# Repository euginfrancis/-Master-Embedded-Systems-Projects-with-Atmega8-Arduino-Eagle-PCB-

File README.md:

# Master Embedded Systems: Projects with Atmega328, Arduino, and Eagle-PCB

Welcome to the **Embedded Systems Projects** repository! This repository contains a collection of projects using the **Atmega328** microcontroller, **Arduino**, and **Eagle PCB design**. These projects are designed for beginners who want to learn embedded systems concepts, build real-world applications, and fabricate their own PCBs.

## Table of Contents

- [Overview](#overview)
- [Understanding Microcontrollers: Atmega328 Basics](#understanding-microcontrollers-atmega8-basics)
- [Compile a C file using WinAVR](#compile-a-c-file-using-winavr)
- [Programming with Arduino IDE](#programming-with-arduino-ide)
- [Installing Arduino IDE and Setting Up ATmega328/UNO Board](#installing-arduino-ide-and-setting-up-atmega328uno-board)
- [Setting Up USBASP Programmer and USB-to-Serial Converter](#setting-up-usbasp-programmer-and-usb-to-serial-converter)
- [Eagle PCB Design: From Schematic to Fabrication](#eagle-pcb-design-from-schematic-to-fabrication)
- [DIY PCB Fabrication Process](#diy-pcb-fabrication-process)
- [HD44780 LCD Communication Protocol](#hd44780-lcd-communication-protocol)

## Overview

This repository provides practical examples of embedded systems projects using the **Atmega328** microcontroller and **Arduino** platform. You will also explore **Eagle PCB design** for creating custom PCBs. The goal is to build a solid foundation for working with embedded systems and PCB fabrication.

## Understanding Microcontrollers: Atmega8 Basics

A **microcontroller** is a compact integrated circuit that acts as the brain of an embedded system. It combines a processor (for executing instructions), memory (for storing programs and temporary data), and input/output pins (for connecting to external devices) all in one chip. Unlike general-purpose computers, microcontrollers are designed to perform specific tasks, such as controlling an appliance, blinking an LED, or reading data from a sensor. Their versatility and low cost make them a cornerstone of modern electronics, found in everything from toys to industrial machinery.

The **Atmega328**, part of the AVR family, is a popular 8-bit microcontroller for beginners. Built on the efficient AVR architecture, it uses a Reduced Instruction Set Computer (RISC) design for faster performance. It features 32 KB of Flash memory for program storage, 1 KB of SRAM for temporary data, and 512 bytes of EEPROM for saving data even when power is off. With 23 input/output pins, built-in timers, a 10-bit Analog-to-Digital Converter (ADC), and communication protocols like UART, SPI, and I2C, the Atmega328 is ideal for learning how microcontrollers work. Its simplicity, combined with powerful features, makes it a go-to choice for building practical projects like motor control, sensor interfacing, and custom PCB designs.

## Compile a C file using WinAVR

To compile a C file using **WinAVR**, follow these steps:

### Step 1: Install WinAVR

Download and install **WinAVR** from its [official site](http://winavr.sourceforge.net/) or a trusted source.  
This package includes:
- **avr-gcc compiler**
- **avrdude**
- Supporting tools

### Step 2: Write the C Program

Create your C program and save it with a `.c` extension. For example, `main.c`.

### Step 3: Create a Makefile

Create a file named `Makefile` in the same directory as your C program.

Here is a simple example of a Makefile:

```makefile
MCU = atmega8       # Target microcontroller (change as needed)
F_CPU = 16000000UL  # Clock frequency
CC = avr-gcc
CFLAGS = -mmcu=$(MCU) -DF_CPU=$(F_CPU) -Wall -Os
TARGET = main

all: $(TARGET).hex

$(TARGET).hex: $(TARGET).elf
	avr-objcopy -O ihex -R .eeprom $(TARGET).elf $(TARGET).hex

$(TARGET).elf: $(TARGET).c
	$(CC) $(CFLAGS) -o $(TARGET).elf $(TARGET).c

clean:
	rm -f *.elf *.hex
```
### Makefile Explanation:

- `MCU`: Specify your microcontroller model (e.g., atmega8, atmega328p).
- `F_CPU`: Specify the frequency of your microcontroller in Hz.
- Replace `main.c` with the name of your C file if different.

### Step 4: Compile the Program

1. Open a command prompt.
2. Navigate to the folder containing your `main.c` and `Makefile`.
3. Run the `make` command:

```bash
make
```
This will compile your code and generate a .hex file ready for uploading to the microcontroller.

### Step 5: Upload to the Microcontroller

Use avrdude to upload the .hex file to your microcontroller. For example:

```bash
avrdude -c usbasp -p atmega8 -U flash:w:main.hex
```
Replace usbasp with your programmer.
Replace atmega8 with your microcontroller model.

### Step 6: Verify the Program

Ensure your microcontroller runs the compiled program as expected.

### Troubleshooting

If you encounter issues:

    Verify the MCU and F_CPU values match your microcontroller.
    Ensure all paths are set correctly in the environment variables if make or avr-gcc is not recognized.

## Programming with Arduino IDE

Arduino provides several built-in functions to interact with hardware components like LEDs, sensors, and motors. Here’s an overview of the most commonly used functions, explained in a simple way.

### `pinMode()`
Configures a GPIO pin as an **input** or **output**.  
- **pin**: The pin number you want to set (e.g., 2, 13).  
- **mode**: Use `INPUT`, `OUTPUT`, or `INPUT_PULLUP`.  

**Example**:  
```cpp
pinMode(13, OUTPUT); // Set pin 13 as output
pinMode(2, INPUT);   // Set pin 2 as input
```
### `digitalWrite()`
Sets a pin to either HIGH (on) or LOW (off).

**Example**:  
```cpp
digitalWrite(13, HIGH); // Turn on LED connected to pin 13
digitalWrite(13, LOW);  // Turn it off
```
### `digitalRead()`
Reads the state of a digital input pin (HIGH or LOW).

**Example**:  
```cpp
int buttonState = digitalRead(2); // Read the state of the button on pin 2
```
### `analogWrite()`
Generates a PWM signal to control the brightness of LEDs or the speed of motors.

value: Ranges from 0 (off) to 255 (full brightness or speed).

**Syntax**:
```cpp
analogWrite(pin, value);
```

**Example**:
```cpp
analogWrite(9, 128); // Set 50% brightness on pin 9
```
### `delay()`
Pauses the program for a specified time in milliseconds.

**Syntax**:
```cpp
delay(milliseconds);
```

**Example**:
```cpp
delay(1000); // Wait for 1 second
```
### `Serial.begin`()
Initializes communication between the Arduino and a computer. The baud rate determines the speed of communication (e.g., 9600 bits per second).

**Syntax**:
```cpp
Serial.begin(baudRate);
```

**Example**:
```cpp
Serial.begin(9600); // Start communication at 9600 bps
```
### `Serial.print() and Serial.println()`
Send data or messages to the computer via the Serial Monitor.
Serial.print(): Prints data on the same line.
Serial.println(): Prints data and moves to the next line.

**Example**:
```cpp
Serial.print("Temperature: ");
Serial.println(25);
```
### `Serial.read()`
Reads incoming data from the serial buffer (one byte at a time).

**Syntax**:
```cpp
char data = Serial.read();
```
**Example**:
```cpp
if (Serial.available() > 0) {
    char receivedData = Serial.read(); // Read the first available byte
}
```

## Installing Arduino IDE and Setting Up ATmega328/UNO Board

This guide provides a brief explanation on how to install the Arduino IDE and set up the **ATmega328** or **Arduino Uno** board.

### 1. Install the Arduino IDE

#### a. Download and Install
1. Visit the official [Arduino website](https://www.arduino.cc/en/software).
2. Download the appropriate version for your operating system (Windows, macOS, Linux).
3. Follow the installation instructions:
   - For Windows: Run the installer `.exe` file and follow the prompts.
   - For macOS: Open the `.dmg` file and drag the Arduino IDE to the Applications folder.
   - For Linux: Use the package manager or install from the tarball.

#### b. Launch the IDE
After installation, launch the **Arduino IDE**. You should see the Arduino IDE window ready for use.

### 2. Set Up the ATmega328/UNO Board in Arduino IDE

#### a. Open the Arduino IDE
1. Open the **Arduino IDE** after installation.

#### b. Select the Board (ATmega328/UNO)
1. Go to **Tools** → **Board** → **Arduino Uno** (which uses the ATmega328P microcontroller).
2. Select **Arduino Uno** from the list of available boards.

#### c. Select the Port
1. Connect your **Arduino Uno** to your computer using a USB cable.
2. Go to **Tools** → **Port** and select the correct port where your Arduino Uno is connected. On Windows, this is usually something like `COM3` or `COM4`. On macOS/Linux, it will show up as `/dev/cu.usbmodemXXXX`.

### 3. Install the ATmega328 Drivers (if needed)

If your Arduino Uno is not recognized or you're using a clone board, you may need to install drivers.

- **For Windows**: The drivers are automatically installed when you install the Arduino IDE. However, for clone boards, you may need to manually install the **CH340/CH341** driver from the manufacturer's website.
- **For macOS/Linux**: These platforms usually don’t require additional drivers. If needed, you can find open-source drivers or use tools like **brew** on macOS.

### 4. Test the Setup

To confirm everything is set up correctly:

1. Open the **Arduino IDE**.
2. Go to **File** → **Examples** → **01.Basics** → **Blink**.
3. Click the **Upload** button (right arrow icon).
4. The LED on pin 13 of the Arduino Uno should start blinking if everything is configured properly.

You have now successfully set up the Arduino IDE for programming the **ATmega328/Uno** board.

## Setting Up USBASP Programmer and USB-to-Serial Converter

This guide explains how to set up the **USBASP programmer** for programming an ATmega328 on a custom PCB and the **USB-to-serial converter** to read data from the board using the **Arduino IDE**.

### 1. Setting Up USBASP Programmer

#### a. Connect the USBASP Programmer to the ATmega328
1. **USBASP Pin Connections**:
   - **MISO** (Master In Slave Out) → **MISO** pin of ATmega328
   - **MOSI** (Master Out Slave In) → **MOSI** pin of ATmega328
   - **SCK** (Serial Clock) → **SCK** pin of ATmega328
   - **RESET** → **RESET** pin of ATmega328
   - **VCC** → **VCC** pin of ATmega328 (5V)
   - **GND** → **GND** pin of ATmega328

2. Ensure that the **USBASP** programmer is securely connected to the **ISP header** (In-System Programming) of your custom PCB.

#### b. Install USBASP Drivers
If your computer does not automatically recognize the **USBASP programmer**, you may need to install drivers:

- **For Windows**: Download and install the **USBASP drivers** from [fischl.de](http://www.fischl.de/usbasp/).
- **For macOS/Linux**: These platforms typically don't require drivers. If needed, you can install **libusb** or use open-source drivers.

#### c. Select USBASP Programmer in Arduino IDE
1. Open **Arduino IDE**.
2. Go to **Tools** → **Programmer** → Select **USBasp**.

### 2. Setting Up USB-to-Serial Converter

#### a. Connect the USB-to-Serial Converter to the ATmega328
To read data from the ATmega328 on your custom PCB, you can use a **USB-to-Serial converter** (e.g., FTDI or CP2102). Here’s how to connect the pins:

1. **USB-to-Serial Pin Connections**:
   - **TX (Transmit)** → **RX** pin of ATmega328
   - **RX (Receive)** → **TX** pin of ATmega328
   - **VCC** → **VCC** pin of ATmega328 (5V)
   - **GND** → **GND** pin of ATmega328
   
2. Make sure the **USB-to-Serial converter** is connected to your PC via USB, and the other side is connected to the ATmega328.

#### b. Select the Serial Port in Arduino IDE
1. Go to **Tools** → **Port** and select the correct COM port for your USB-to-Serial device.
   - On Windows, this could be something like `COM3` or `COM4`.
   - On macOS/Linux, it will be `/dev/cu.usbserial-xxxx`.

#### c. Upload Code and Read Data via Serial Monitor
1. Write your program in **Arduino IDE** and upload it to the ATmega328.
2. Open **Tools** → **Serial Monitor** in Arduino IDE to view data transmitted via **Serial Communication**.
3. Use `Serial.print()` or `Serial.println()` in your program to send data to the **Serial Monitor**.

### 3. Uploading the Program to the ATmega328

### a. Using USBASP Programmer
1. Connect the **USBASP** programmer to your custom PCB.
2. Select **Tools** → **Board** → **Arduino Uno** (for ATmega328).
3. Select **Tools** → **Programmer** → **USBasp**.
4. Click the **Upload Using Programmer** button (Shift + Upload button) to upload the code to the ATmega328.

#### b. Reading Data via Serial Monitor
1. Once the code is uploaded, you can monitor the output of your ATmega328 using **Serial Monitor** (set baud rate as per your code, e.g., 9600).
2. Use `Serial.print()` in your program to send real-time data to the Serial Monitor for debugging or display purposes.

### 4. Troubleshooting

- **USBASP Not Recognized**: If your **USBASP** is not recognized, ensure the drivers are properly installed. On Windows, check for any driver conflicts in the **Device Manager**.
- **No Output on Serial Monitor**: If you're not seeing data in the **Serial Monitor**, check the **TX/RX** connections between the **USB-to-Serial converter** and the **ATmega328**. Also, ensure the baud rate in the `Serial.begin()` matches the baud rate set in the **Serial Monitor**.

## Eagle PCB Design: From Schematic to Fabrication

This guide explains how to use **Eagle PCB Design Software** to create a schematic, design a PCB, and prepare it for fabrication.

### 1. Creating the Schematic in Eagle

1. **Open Eagle Software** and create a new project.
2. In the **Control Panel**, right-click on the project folder and select **New** → **Schematic**.
3. Add components by clicking on the **Add Part** tool, search for components (e.g., resistors, capacitors, ICs) from the libraries.
4. Use the **Wire** tool to connect the components as per your circuit design.
5. Label your nets using the **Label** tool to make the connections clear.
6. Once the schematic is complete, run the **ERC (Electrical Rule Check)** to ensure there are no errors in the design.

### 2. Designing the PCB Layout

1. After completing the schematic, switch to the **PCB Layout** by clicking on the **Switch to Board** button.
2. Eagle will automatically create a board outline, but you can customize it according to your needs.
3. Arrange the components on the board, making sure to keep routing clean and components placed logically.
4. Use the **Route** tool to draw the PCB traces, connecting the components' pins.
5. Add a **Ground Plane** using the **Polygon** tool to reduce noise and improve stability.

### 3. Checking and Finalizing the Design

1. Run the **DRC (Design Rule Check)** to verify that the traces and components meet the fabrication requirements (e.g., trace width, spacing).
2. Use the **Electrical Rule Check (ERC)** to ensure there are no electrical issues.
3. Once everything looks good, generate the **Gerber Files** required for PCB fabrication.

### 4. Fabricating the PCB

1. Export the Gerber files by going to **File** → **CAM Processor**, then selecting the required file outputs (e.g., **Top Layer**, **Bottom Layer**, **Solder Mask**, **Drill Files**).
2. Send the Gerber files to a PCB fabrication service. There are several online services available for custom PCB manufacturing.
3. After the PCB is fabricated, you can solder the components and test the board for functionality.

## DIY PCB Fabrication Process

This guide will walk you through the steps for fabricating a **Printed Circuit Board (PCB)** at home using a **laser printer**, **iron box (clothes iron)**, **ferric chloride (etchant)**, and manual drilling for holes.

### Materials Needed:
- **Laser Printer** (for printing your PCB design)
- **Parchment Paper** (or glossy photo paper)
- **Iron Box** (for transferring toner to the PCB)
- **Ferric Chloride Solution** (for etching the PCB)
- **Copper-Clad PCB Board** (for the base material)
- **Fine Sandpaper** (to clean the PCB)
- **Drill** (for manually drilling holes)
- **Acetone** (for cleaning the PCB)
- **Masking Tape** (optional, to hold the paper in place)

### Step 1: Design the PCB

1. **Create the PCB Design**: Use PCB design software like **Eagle**, **KiCad**, or **EasyEDA** to design your circuit schematic and PCB layout.
2. **Export the Design**: Once your design is ready, export it as a **mirror image** (in Gerber or PDF format) to ensure proper alignment during the transfer.

### Step 2: Print the PCB Design

1. **Print the Design**: Print your mirrored PCB design onto **glossy photo paper** or **parchment paper** using a **laser printer**. Inkjet printers won't work for this method because toner is required to transfer to the PCB.
2. **Print at High Quality**: Ensure you select the highest print quality and set the paper to **no scaling** to preserve the exact size of your design.

### Step 3: Prepare the Copper-Clad PCB

1. **Clean the PCB**: Use **fine sandpaper** to gently sand the surface of the **copper-clad PCB**. This helps the toner adhere better.
2. **Clean the Board**: After sanding, clean the board with **acetone** or rubbing alcohol to remove any grease, dust, or debris.

### Step 4: Transfer the Toner

1. **Position the Printed Design**: Place the printed design (toner side down) onto the copper surface of the PCB. Ensure it aligns correctly.
2. **Secure the Paper**: Use **masking tape** to hold the paper in place if necessary.
3. **Iron the Paper onto the PCB**:
   - Preheat the **iron box** to a medium-high heat setting (no steam).
   - Press the iron firmly onto the paper for about **3-5 minutes**, ensuring that the heat is evenly distributed over the entire design.
   - Apply even pressure and make small circular movements to ensure good contact.
4. **Check the Transfer**: After a few minutes, peel off the paper. The toner should have transferred to the PCB, leaving the copper areas exposed for etching.

### Step 5: Etch the PCB

1. **Prepare Ferric Chloride Solution**: Mix **ferric chloride** with water (usually 1 part ferric chloride to 3 parts water). You can use a plastic or glass container to hold the solution.
2. **Submerge the PCB**: Place the PCB in the **ferric chloride solution**. Gently agitate the container to help the etching process.
3. **Wait for the Etching Process**: The ferric chloride will dissolve the exposed copper, leaving the toner-protected copper traces intact. This usually takes about **30 minutes to 1 hour**.
4. **Check Progress**: Periodically check the progress. Once all the exposed copper is etched away and only the toner traces remain, remove the PCB from the solution.

### Step 6: Clean and Finalize the PCB

1. **Remove the Toner**: After etching, the PCB will be covered in toner. Use **acetone** to remove the toner and reveal the copper traces.
2. **Drill Holes**: For components that require through-hole connections, carefully drill the holes using a small **drill bit**. You can use a handheld drill or a Dremel tool.
   - Make sure to use the correct bit size for the components' lead diameter.
   - Keep the PCB steady and drill at a slow speed to avoid damaging the traces.

### Step 7: Inspect the PCB

1. **Inspect for Errors**: Carefully inspect the PCB for any missed connections, broken traces, or incomplete etching. You can fix minor issues with **conductive ink** or **wire bridges**.
2. **Test the PCB**: Before soldering components, it's a good idea to test the board with a multimeter to ensure the traces and connections are correct.

### Conclusion

Congratulations! You've just fabricated your own **PCB** at home. Now, you can proceed with **soldering the components** onto the PCB, and your custom circuit is ready to be used. While this process can take some time, it's a great and cost-effective way to create your own PCBs without needing a professional service.

## HD44780 LCD Communication Protocol

### Initialization Sequence (Setting up the LCD)

```mermaid
sequenceDiagram
    participant MCU
    participant LCD

    MCU->>LCD: Send Function Set (e.g., 0x38)
    LCD->>MCU: Acknowledge

    MCU->>LCD: Send Display ON/OFF (e.g., 0x0C)
    LCD->>MCU: Acknowledge

    MCU->>LCD: Send Clear Display Command (e.g., 0x01)
    LCD->>MCU: Acknowledge

    MCU->>LCD: Send Entry Mode Set (e.g., 0x06)
    LCD->>MCU: Acknowledge

    MCU->>LCD: Send Cursor Home Command (e.g., 0x02)
    LCD->>MCU: Acknowledge

    MCU->>MCU: LCD Initialized

```
### Write Command Sequence (Sending Command to LCD)

```mermaid
sequenceDiagram
    participant MCU
    participant LCD

    MCU->>LCD: Send Command (e.g., 0x80 for setting cursor)
    LCD->>MCU: Acknowledge
    MCU->>LCD: Send Command Data (e.g., character or special instruction)
    LCD->>MCU: Acknowledge
    MCU->>MCU: Command Executed (cursor moved or action performed)
```

### Read Command Sequence (Reading Status or Data from LCD)

```mermaid
sequenceDiagram
    participant MCU
    participant LCD

    MCU->>LCD: Send Read Command (e.g., 0x80 for status)
    LCD->>MCU: Provide Busy Flag (if LCD is busy)
    
    MCU->>LCD: Send Data Read Command (e.g., 0x00 for data register)
    LCD->>MCU: Return Data (e.g., character from display)
    MCU->>MCU: Read Data Successfully
```

### Write Data String Sequence (Sending a Data String to LCD for Display)

```mermaid
sequenceDiagram
    participant MCU
    participant LCD

    MCU->>LCD: Send Data (e.g., First Character)
    LCD->>MCU: Acknowledge
    MCU->>LCD: Send Next Data Character
    LCD->>MCU: Acknowledge
    loop Write Entire String
        MCU->>LCD: Send Character
        LCD->>MCU: Acknowledge
    end
    MCU->>MCU: Data String Displayed on LCD
```

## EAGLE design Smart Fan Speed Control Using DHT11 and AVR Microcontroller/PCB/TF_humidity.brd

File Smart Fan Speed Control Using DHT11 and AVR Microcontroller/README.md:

# Smart Fan Speed Control Using DHT11 and AVR Microcontroller

This project demonstrates how to control the speed of a fan based on room temperature readings from a **DHT11 sensor**. The speed of the fan is controlled using **Pulse Width Modulation (PWM)** through an **AVR microcontroller**. This guide explains how to set up the hardware and software for this project, along with the necessary flashing and PCB creation steps.

## Components Used
- **AVR Microcontroller** (e.g., ATmega328P)
- **DHT11 Temperature and Humidity Sensor**
- **PWM-Controlled Fan**
- **NPN Transistor (e.g., 2N2222) or MOSFET** (for controlling the fan)
- **Resistors, Capacitors, and other Passive Components**

## DHT11 Sensor Details

The **DHT11** sensor is a basic, low-cost digital sensor used for measuring temperature and humidity. It communicates with a microcontroller using a **single-wire digital interface**, sending data as a **serial stream** of 40 bits.

### Key Features of DHT11:
- **Temperature Range**: 0°C to 50°C (accuracy: ±2°C)
- **Humidity Range**: 20% to 90% RH (accuracy: ±5% RH)
- **Output**: Digital (serial)
- **Operating Voltage**: 3.5V to 5.5V

### DHT11 Communication Protocol
The DHT11 sensor uses a **single-wire communication protocol** to transmit data. The sensor sends data in **40 bits**:
1. **Humidity (16 bits)**: The first 16 bits represent humidity data.
2. **Temperature (16 bits)**: The next 16 bits represent temperature data.
3. **Checksum (8 bits)**: The last 8 bits are a checksum to verify the accuracy of the data.

To communicate with the DHT11 sensor, the microcontroller sends a **start signal** to the sensor, which responds with the requested data.

### DHT11 Communication Sequence Diagram

```mermaid
%% Example of a timing diagram for a start signal
sequenceDiagram
    participant MCU
    participant Sensor
    
    MCU->>Sensor: Send Start Signal (18ms Low)
    Sensor->>MCU: Respond (80µs Low, 80µs High)
    MCU->>Sensor: Wait for Data
    Sensor->>MCU: Send Data (40 bits)
    MCU->>MCU: Validate Data Integrity
    MCU->>Sensor: Return Success/Failure

```

## Project Overview

This project reads the room temperature from the DHT11 sensor, then adjusts the fan speed accordingly using **PWM**. The fan speed increases with higher temperatures, providing an effective and efficient cooling system. The control is implemented using an **AVR microcontroller** (e.g., ATmega328P) which reads the DHT11 sensor and adjusts the PWM signal for fan control.

## Flashing the Code
To flash the code to your AVR microcontroller, you can follow the instructions below:

Install WinAVR:

WinAVR includes the avr-gcc compiler and other tools required to program your AVR microcontroller. Follow the installation guide in the main repository README.

## Program the Microcontroller:

For Arduino: You can use the Arduino IDE to upload the code to your AVR microcontroller. Select the correct board and port in the Tools menu, then click Upload.

For WinAVR: Open a command prompt and use avr-gcc and avrdude to compile and upload the code. Example:

```bash
avr-gcc -mmcu=atmega328p -o program.elf program.c
avr-objcopy -O ihex program.elf program.hex
avrdude -c usbasp -p m328p -U flash:w:program.hex
```
## Flashing Details and Custom PCB Creation

For detailed flashing instructions, please refer to the main repository README.

## Custom PCB Creation: 

If you wish to create a custom PCB for this project, you can follow the steps provided in the main repository. The PCB design can be created using Eagle PCB as outlined in the repository.

## Troubleshooting
If the fan does not adjust speed:

Verify that the PWM pin is properly connected.
Ensure that the DHT11 sensor is connected correctly to the microcontroller.
Check if the microcontroller is properly powered.
If the DHT11 sensor gives inaccurate readings:

Ensure that the DHT11 sensor is connected properly.
Confirm that the sensor's data line is connected to the correct digital pin.

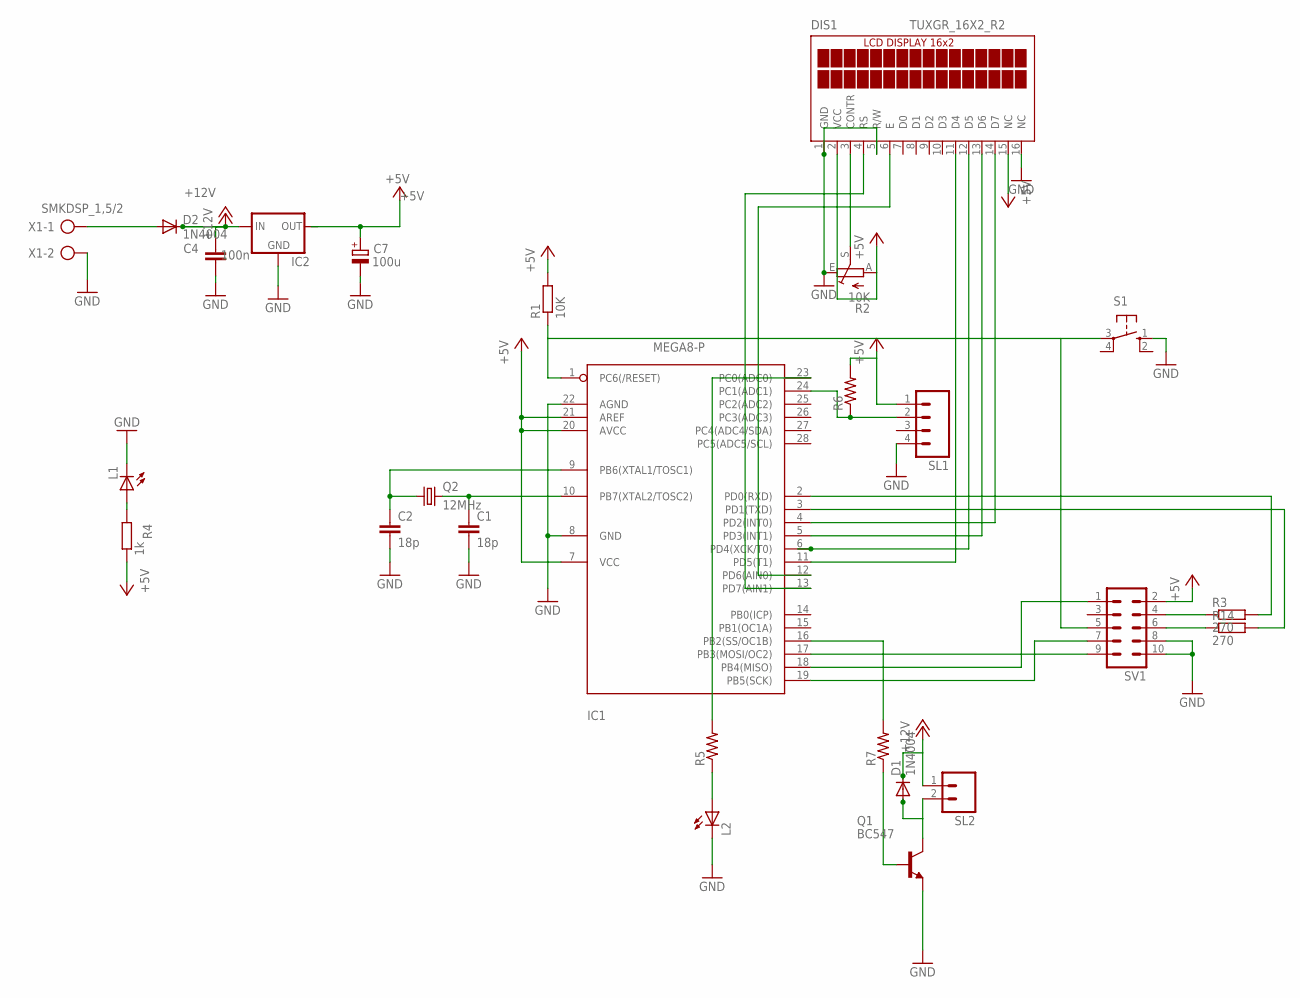
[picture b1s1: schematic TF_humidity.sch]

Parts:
C1, C2: 18p; C025-024X044
C4: 100n; C025-030X050
C7: 100u; E3,5-8
D1, D2: 1N4004; DO41-10
DIS1: TUXGR_16X2_R2
IC1: MEGA8-P; DIL28-3
IC2: 78XXS
L1, L2: LED5MM
Q1: BC547; TO92
Q2: 12MHz; HC49/S
R1: 10K; 0207/10
R2: 10K; CA6V
R3, R14: 270; 0207/10
R4: 1k; 0207/10
R5, R6, R7: R-US_0207/10; 0207/10
S1: 10-XX; B3F-10XX
SL1: M04; 04P
SL2: M02; 02P
SV1: ML10
X1: SMKDSP_1,5/2

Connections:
+5V: C7.+, DIS1.2 (VCC), DIS1.15 (NC), IC1.7 (VCC), IC1.20 (AVCC), IC1.21 (AREF), IC2.OUT, R1.2, R2.A, R4.2, R6.2, SL1.1, SV1.2
+12V: C4.2, D1.C, D2.C, IC2.IN, SL2.1
GND: C1.2, C2.2, C4.1, C7.-, DIS1.1 (GND), DIS1.5 (R/W), DIS1.16 (NC), IC1.8 (GND), IC1.22 (AGND), IC2.GND, L1.K (C), L2.K (C), Q1.1 (E), R2.E, S1.1 (S), SL1.4, SV1.8, SV1.10, X1.2
unnamed: L1.A, R4.1
unnamed: DIS1.6 (E), IC1.12 (PD6(AIN0))
unnamed: C1.1, IC1.10 (PB7(XTAL2/TOSC2)), Q2.2
unnamed: C2.1, IC1.9 (PB6(XTAL1/TOSC1)), Q2.1
unnamed: DIS1.3 (CONTR), R2.S
unnamed: R3.1, SV1.4
unnamed: IC1.2 (PD0(RXD)), R3.2
unnamed: D1.A, Q1.3 (C), SL2.2
unnamed: DIS1.13 (D6), IC1.5 (PD3(INT1))
unnamed: DIS1.14 (D7), IC1.4 (PD2(INT0))
unnamed: IC1.18 (PB4(MISO)), SV1.1
unnamed: DIS1.12 (D5), IC1.6 (PD4(XCK/T0))
unnamed: IC1.1 (PC6(/RESET)), R1.1, S1.3, SV1.5
unnamed: DIS1.11 (D4), IC1.11 (PD5(T1))
unnamed: IC1.17 (PB3(MOSI/OC2)), SV1.9
unnamed: L2.A, R5.1
unnamed: IC1.16 (PB2(SS/OC1B)), R7.2
unnamed: IC1.23 (PC0(ADC0)), R5.2
unnamed: IC1.24 (PC1(ADC1)), R6.1, SL1.2
unnamed: D2.A, X1.1
unnamed: IC1.3 (PD1(TXD)), R14.2
unnamed: R14.1, SV1.6
unnamed: DIS1.4 (RS), IC1.13 (PD7(AIN1))
unnamed: Q1.2 (B), R7.1
unnamed: IC1.19 (PB5(SCK)), SV1.7

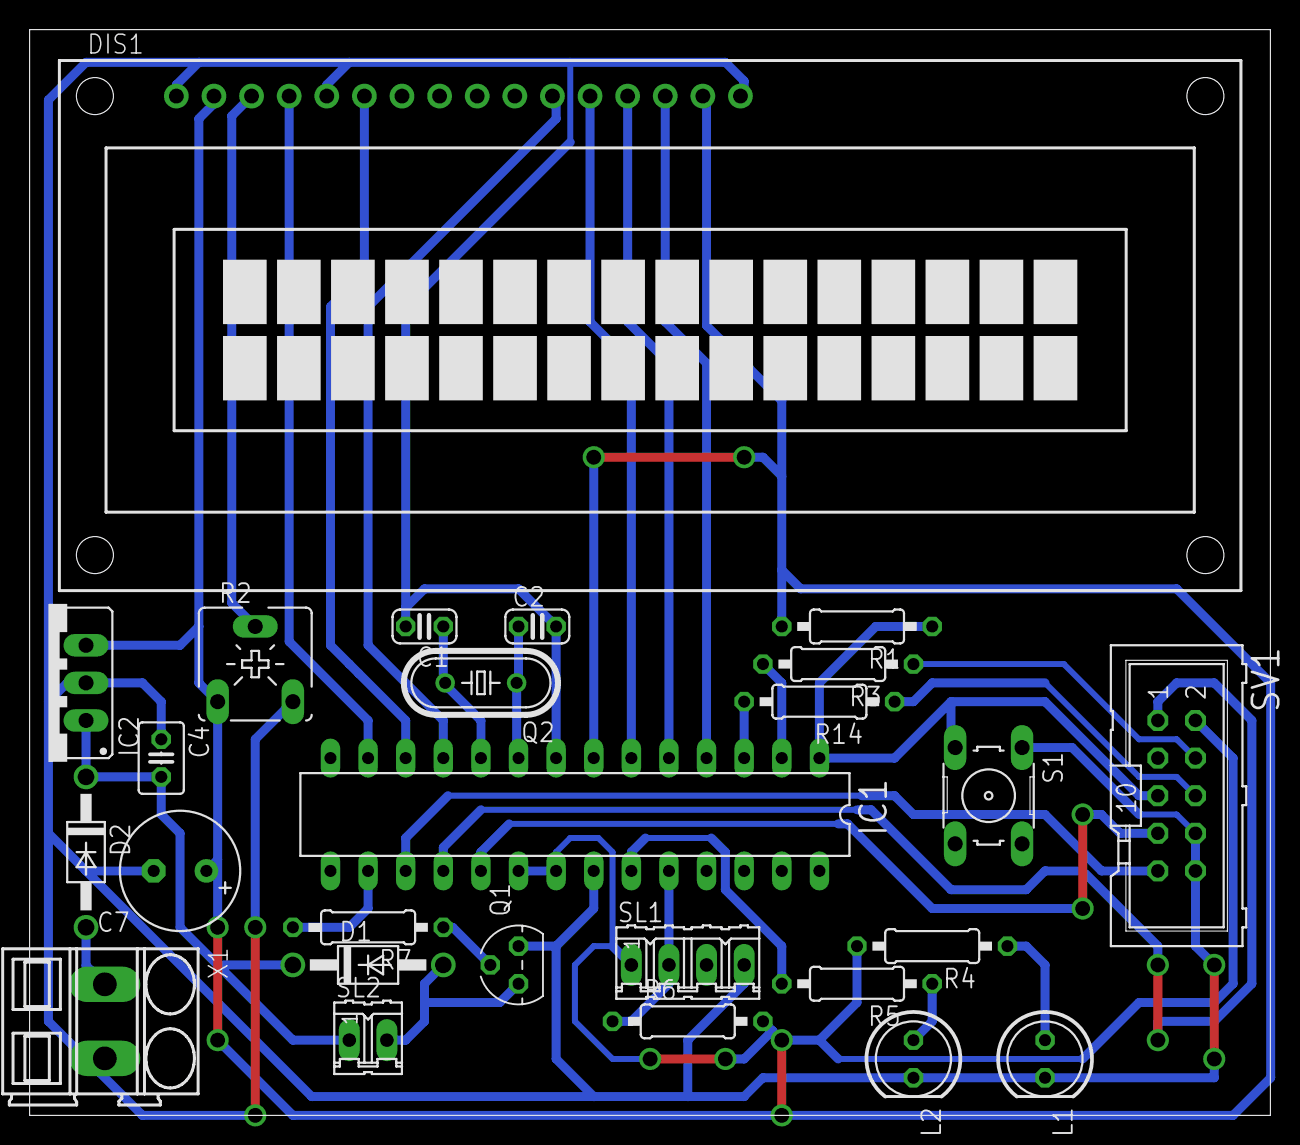
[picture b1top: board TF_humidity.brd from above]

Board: 2 copper layers, 83.8 x 73.3 mm, 26 parts (0 on the bottom side), 28 nets.

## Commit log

2024-11-25 dht11
2024-11-26 Rename REAMDE.md to README.md
